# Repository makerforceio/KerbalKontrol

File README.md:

# KerbalKontrol
Kerbal Space Program is a popular space simulator game which we at MakerForce been enjoying for a while. So, we decided
to just go build an arcade like console for it. This project was fortunate enough to be featured on [Hackaday](), and you
can check out the original blog post [here](https://makerforce.io/the-ksp-command-station-2/).

# Implementation
This control station is based fully upon the ATMEGA328 as its primary MCU. It is powered by 2 custom designed PCBs - the IO-Board and the Main-Board. The IO-Board is connected to each panel and contains a single MCU + shift registers. All of the IO-Boards are wired to the Main-Board using RJ45 conns and ethernet cables. The communication bus within is currently I2C but we want to switch to D-I2C in the future. All of the IO-Boards are configured as I2C Slaves and the Main-Board is the single master.

The internal switches, lights are wired up to the boards through the header connectors visible on the IO-Board.

# Software
Everything is programmed using avr-libc with no external libraries. 

## Compile from source
To compile from source for the IO-Board and Main-Board, follow the steps below.

```
git clone https://www.github.com/solderneer/KerbalKontrol
cd code/io-board
make
```

```
git clone https://www.github.com/solderneer/KerbalKontrol
cd code/main-board
make
```
The directory can simply be cleaned with this command.

```
make clean
```

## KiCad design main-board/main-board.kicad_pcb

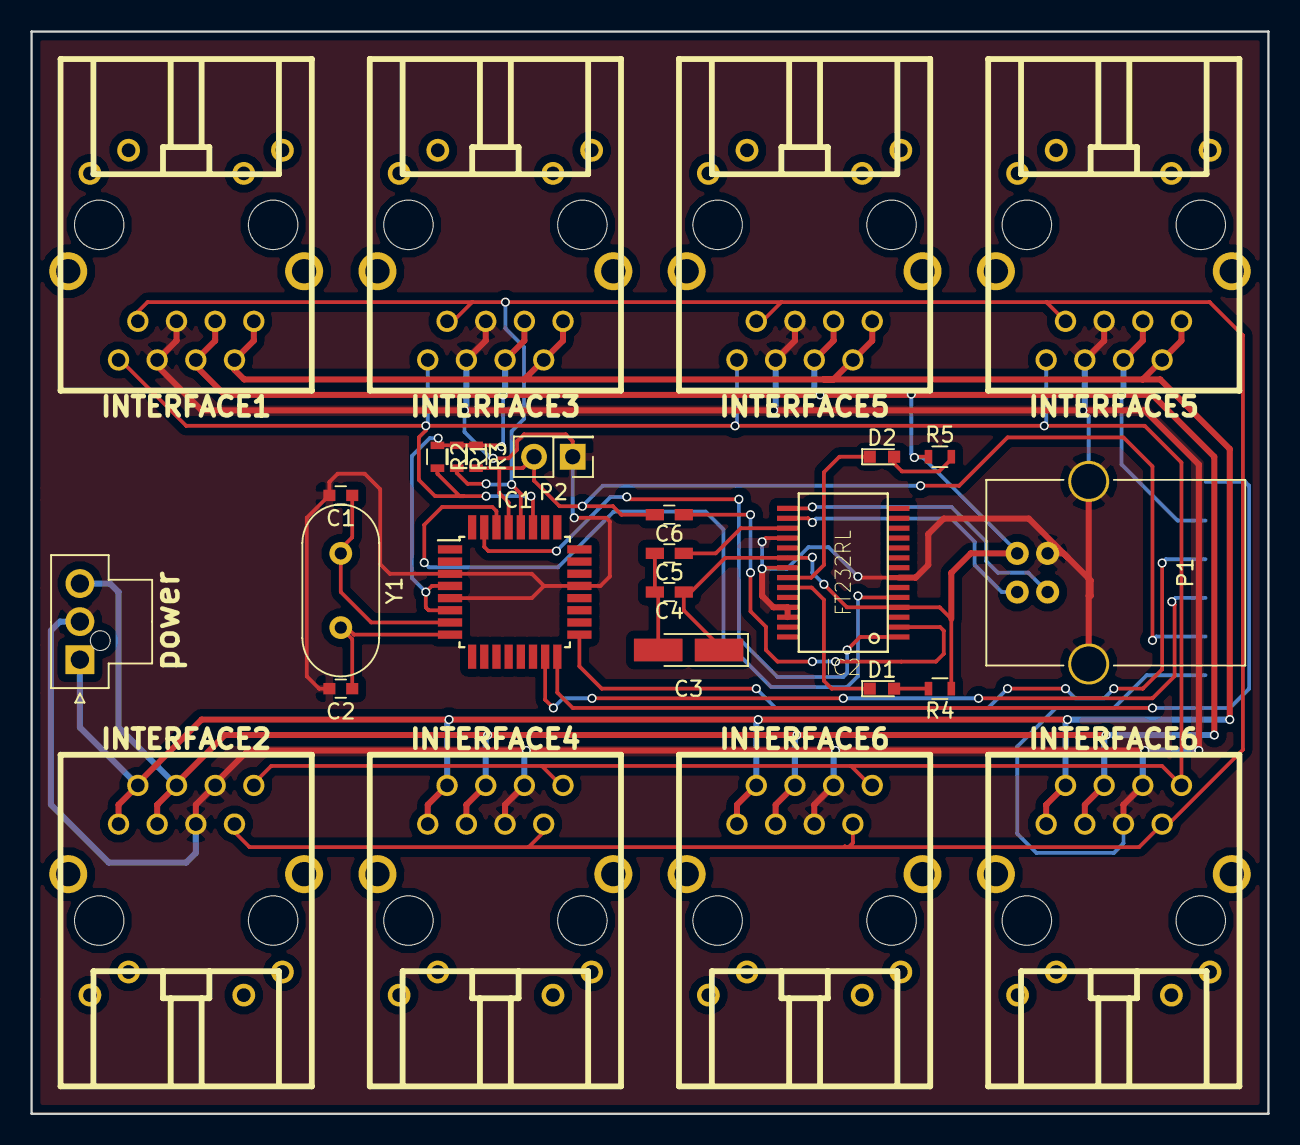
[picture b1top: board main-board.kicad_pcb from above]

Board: 2 copper layers, 81.3 x 71.1 mm, 18 parts (0 on the bottom side), 18 nets.

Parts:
C1, C2: C; C_0603
C3: 10uF; CP_Tantalum_Case-S_EIA-3216-12_Hand
C4, C5: 0.1uF; C_0603_HandSoldering
C6: 100nF; C_0603_HandSoldering
D1, D2: LED; LED_0603
IC1: ATMEGA328-A; TQFP-32_7x7mm_Pitch0.8mm
IC2: FT232RL; SSOP28-LD
P1: USB_B
P2: CONN_01X02; Pin_Header_Straight_2x01_Pitch2.54mm
R1, R2: R; R_0603
R3: 10K; R_0603
R4, R5: 1K; R_0603
Y1: Crystal; Crystal_HC49-U_Vertical

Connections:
+3V3: C5.1, IC2.17
+5V: C3.1, C4.1, IC1.4, IC1.6, IC2.4, IC2.20, P1.1, R1.1, R2.1, R3.1, R4.1, R5.1
DTR: C6.1, IC2.2
GND: C1.2, C2.2, IC1.3, IC1.5, IC1.21, IC2.7, IC2.18, IC2.21, IC2.25, IC2.26, P1.4, P1.5, P2.1
unnamed: C3.2, C4.2, C5.2
unnamed: D1.1, IC2.23
unnamed: D1.2, R4.2
unnamed: D2.1, IC2.22
unnamed: D2.2, R5.2
unnamed: IC2.15, P1.3
unnamed: IC2.16, P1.2
RST: C6.2, IC1.29, P2.2, R3.2
RX1: IC1.30, IC2.5
SCL: IC1.28, R1.2
SDA: IC1.27, R2.2
TX1: IC1.31, IC2.1
XTAL1: C1.1, IC1.7, Y1.1
XTAL2: C2.1, IC1.8, Y1.2

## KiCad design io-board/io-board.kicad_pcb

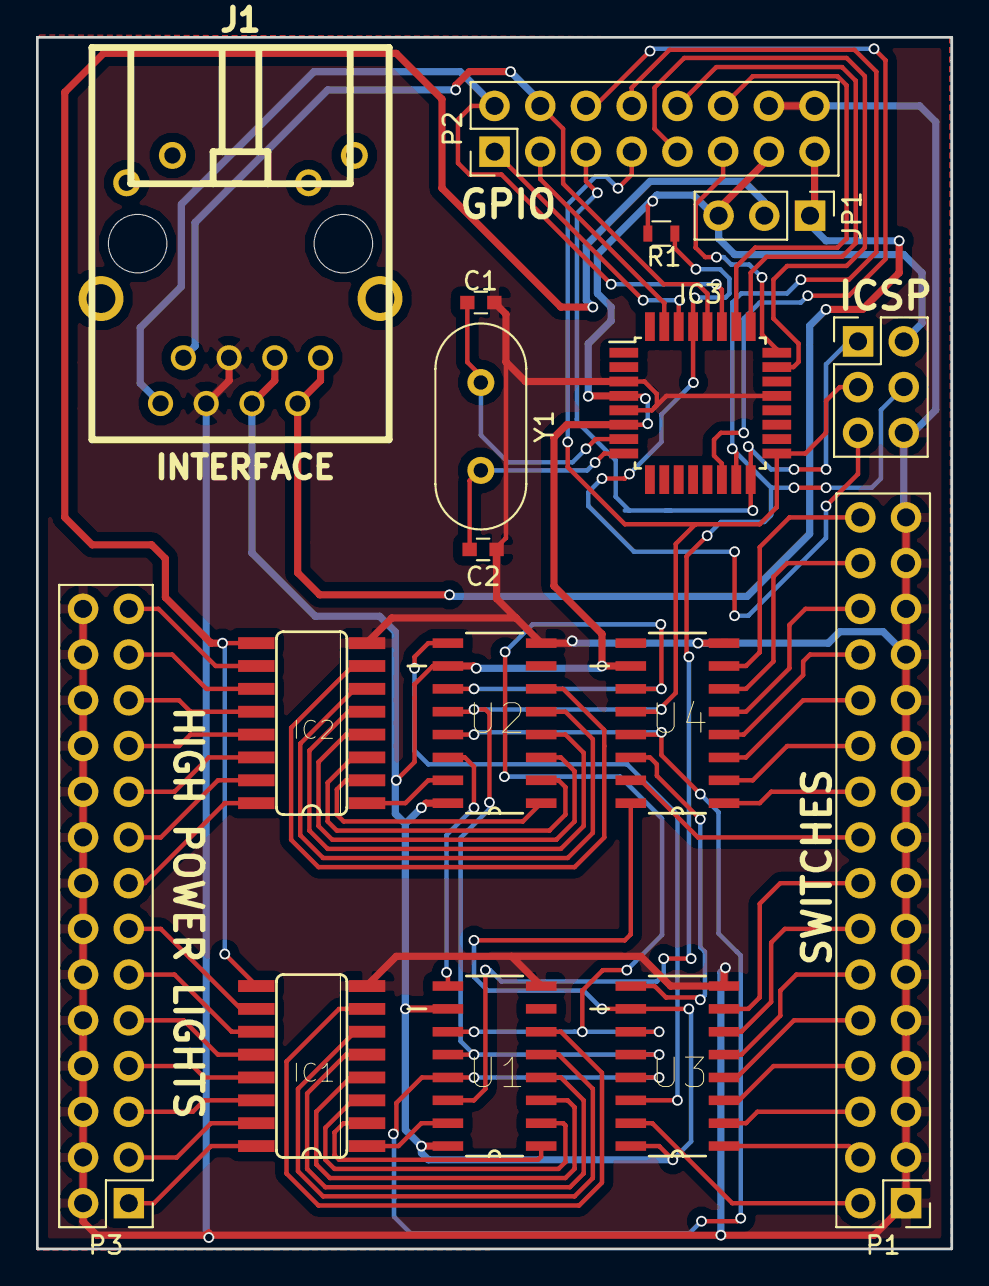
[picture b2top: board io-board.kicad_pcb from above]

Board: 2 copper layers, 50.8 x 67.3 mm, 16 parts (0 on the bottom side), 68 nets.

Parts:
C1, C2: C_0603
IC1, IC2: SO16
IC3: TQFP-32_7x7mm_Pitch0.8mm
J1: INTERFACE; rj45-wiznet-rb1-125bag1a
JP1: Pin_Header_Straight_1x03_Pitch2.54mm
P1: Pin_Header_Straight_2x16_Pitch2.54mm
P2: Pin_Header_Straight_2x08_Pitch2.54mm
P3: LIGHTS; Pin_Header_Straight_2x14_Pitch2.54mm
R1: R_0603
U1, U2, U3, U4: SOIC127P600X175-16N
Y1: Crystal_HC49-4H_Vertical

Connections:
+5V: IC3.4, IC3.6, J1.3, J1.4, JP1.3, P2.13, R1.1, U1.10, U1.16, U2.10, U2.16, U3.10, U3.16, U4.10, U4.16
+12V: J1.1, J1.2, JP1.1, P2.15
/L1: IC1.16, P3.1
/L2: IC1.15, P3.3
/L3: IC1.14, P3.5
/L4: IC1.13, P3.7
/L5: IC1.12, P3.9
/L6: IC1.11, P3.11
/L7: IC1.10, P3.13
/L8: IC2.16, P3.15
/L9: IC2.15, P3.17
/L10: IC2.14, P3.19
/L11: IC2.13, P3.21
/L12: IC2.12, P3.23
/L13: IC2.11, P3.25
/L14: IC2.10, P3.27
/LIGHT_POWER: IC1.9, IC2.9, JP1.2
/OE: U1.13, U2.13, U3.13, U4.13
/RCLK: U1.11, U2.11, U3.11, U4.11
/SW1: P1.2, U3.15
/SW2: P1.4, U3.1
/SW3: P1.6, U3.2
/SW4: P1.8, U3.3
/SW5: P1.10, U3.4
/SW6: P1.12, U3.5
/SW7: P1.14, U3.6
/SW8: P1.16, U3.7
/SW9: P1.18, U4.15
/SW10: P1.20, U4.1
/SW11: P1.22, U4.2
/SW12: P1.24, U4.3
/SW13: P1.26, U4.4
/SW14: P1.28, U4.5
/SW15: P1.30, U4.6
/SW16: P1.32, U4.7
ADC0: IC3.23, P2.9
ADC1: IC3.24, P2.11
ADC2: IC3.25, P2.10
ADC3: IC3.26, P2.12
GND: C1.1, C2.1, IC1.8, IC2.8, IC3.3, IC3.5, IC3.21, J1.5, J1.6, P1.1, P1.3, P1.5, P1.7, P1.9, P1.11, P1.13, P1.15, P1.17, P1.19, P1.21, P1.23, P1.25, P1.27, P1.29, P1.31, P2.14, P2.16, P3.2, P3.4, P3.6, P3.8, P3.10, P3.12, P3.14, P3.16, P3.18, P3.20, P3.22, P3.24, P3.26, P3.28, U1.8, U2.8, U3.8, U4.8
MISO: IC3.16, P2.5
MOSI: IC3.15, P2.8, U1.14
unnamed: IC1.1, U1.15
unnamed: IC1.2, U1.1
unnamed: IC1.3, U1.2
unnamed: IC1.4, U1.3
unnamed: IC1.5, U1.4
unnamed: IC1.6, U1.5
unnamed: IC1.7, U1.6
unnamed: IC2.1, U2.15
unnamed: IC2.2, U2.1
unnamed: IC2.3, U2.2
unnamed: IC2.4, U2.3
unnamed: IC2.5, U2.4
unnamed: IC2.6, U2.5
unnamed: IC2.7, U2.6
unnamed: U1.9, U2.14
unnamed: U2.9, U3.14
unnamed: U3.9, U4.14
RST: IC3.29, R1.2
RX1: IC3.30, P2.1
SCK: IC3.17, P2.7, U1.12, U2.12, U3.12, U4.12
SCL: IC3.28, J1.7, P2.4
SDA: IC3.27, J1.8, P2.2
SS: IC3.14, P2.6
TX1: IC3.31, P2.3
XTAL1: C1.2, IC3.7, Y1.1
XTAL2: C2.2, IC3.8, Y1.2

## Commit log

2017-05-15 started work on the schematic
2017-05-15 finished schematics for io-board
2017-05-15 started working on the main-board
2017-05-15 finished the schematics for main-board
2017-05-15 started routing io-board
2017-05-15 finished routing io-board
2017-05-15 added PDF for schematics & pcb layout
2017-05-16 fixed some routing
2017-05-16 started routing main-board
2017-05-16 finidhed routing the main-board
2017-05-18 final commit with proper silkscreen and pdf exports
2017-05-20 Add branding
2017-05-23 finished fixes for the board
2017-05-23 finished fixes for io-board
2017-05-23 Update gerbers and branding
2017-05-25 added BOM without Digikey part numbers
2017-05-26 MEOW
2017-05-27 finished BOM
2017-05-28 reorganised directories
2017-06-15 initialize the code base
2017-06-16 configured the sublime.project for proper autocomplete and linting
2017-06-16 Update gitignore
2017-06-16 letting the gitignore do its thing
2017-06-16 added blinky code as example on toggling GPIO
2017-06-16 tracking some random things
2017-06-20 learning AVR, don't mind me
2017-06-22 added gpio init function
2017-06-27 added gpio pin intialization function
2017-07-03 added IO functions
2017-07-03 finish IO_Init function
2017-07-03 finish IO_Write function
2017-07-03 finish IO_Toggle/Set/Reset
2017-07-03 finish implementing IO abstraction
2017-07-03 added SPI functions
2017-07-03 finish SPI_Init
2017-07-03 added in ISR
2017-07-03 added in SPI_Write
2017-07-03 finish implementing SPI abstraction
2017-07-03 tested compile
2017-07-03 switches
2017-07-03 added switches.c
2017-07-03 committing everything
2017-07-04 need to write shift register driver first
2017-07-04 partially implemented shift register driver
2017-07-04 finished implementing 75hc595 drivers
2017-07-04 finished with switches
2017-07-05 fixed the switch scanning code
2017-07-05 removed old code from main.c
2017-07-05 updated Makefile and added test code
2017-07-05 removed some test code
2017-07-05 adding test code for shift register
2017-07-06 cleaned up Makefile
2017-07-08 committing latest code
2017-07-09 incremental changes
2017-07-10 started work on the i2c abstraction
2017-07-10 implemented driver adapter interface for i2c
2017-07-10 added i2c initialisation code
2017-07-10 finished i2c driver
2017-07-10 added I2C status state machine
2017-07-10 final commit for this project today
2017-07-10 populating the driver code for main-board from io-board
2017-07-10 updated settings.h to latest clock rate
2017-07-11 bodged the hardware board, testing Shift code
2017-07-11 incremental changes to shifting code
2017-07-16 updated io-board code
2017-07-16 fixing IO board
2017-07-16 figured out problem with DDRx function argument
2017-07-16 more problems with Shift reg
2017-07-16 problem is within spi
2017-07-19 switch to no-spi peripheral
2017-07-19 no idea what is going on
2017-07-21 rough I2C implementation
2017-07-21 starting to populate the I2C
2017-07-21 finished up io-board firmware
2017-07-22 wth, tx & rx flipped
2017-08-01 Fixes #11 (library paths)
2017-08-22 committing latest changes
2017-10-26 removed sublime text projects
2017-10-26 specified correct target mmcu
2017-11-03 prob final commit
